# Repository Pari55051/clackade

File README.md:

# 🎮 Clackade — LED the games begin!
a mini arcade in a gameboy style look, with 4 games inter-switchable by long-pressing the first button.

---

## Included Games

1. Simon Says: memory game where a sequence is shown and you have to press the exact same one

2. Whack-a-LED: click the corresponding button to the led before the timer runs out (like Whack a Mole)

3. LED Chase: use the D-pad shaped buttons to navigate to the glowing led as fast as possible

4. Code Cracker: try to guess a randomly code like a detective

---

## Images (or screenshots :P)

### Schematic

---

### PCB Layout

---

### 3D View

---

## How It Works (also acts as a BOM)

- Microcontroller: Seeed XIAO RP2040  
- Buttons: 4x tactile keyboard keys
- LEDs: 4x single-color (+ resistors)
- Mode Switching: Long press on top button triggers the game select loop

---

## Credits

- Made by [U.N. Owen](https://github.com/pari55051)
- Slack ID:  U08TH3JV9V4 (for hackclub's slack)
- Made for: [Pathfinder - Hackclub's YSWS](http://pathfinder.hackclub.com/)

> the drill and gerber files are in the production folder in folders drill an gerbers respectively

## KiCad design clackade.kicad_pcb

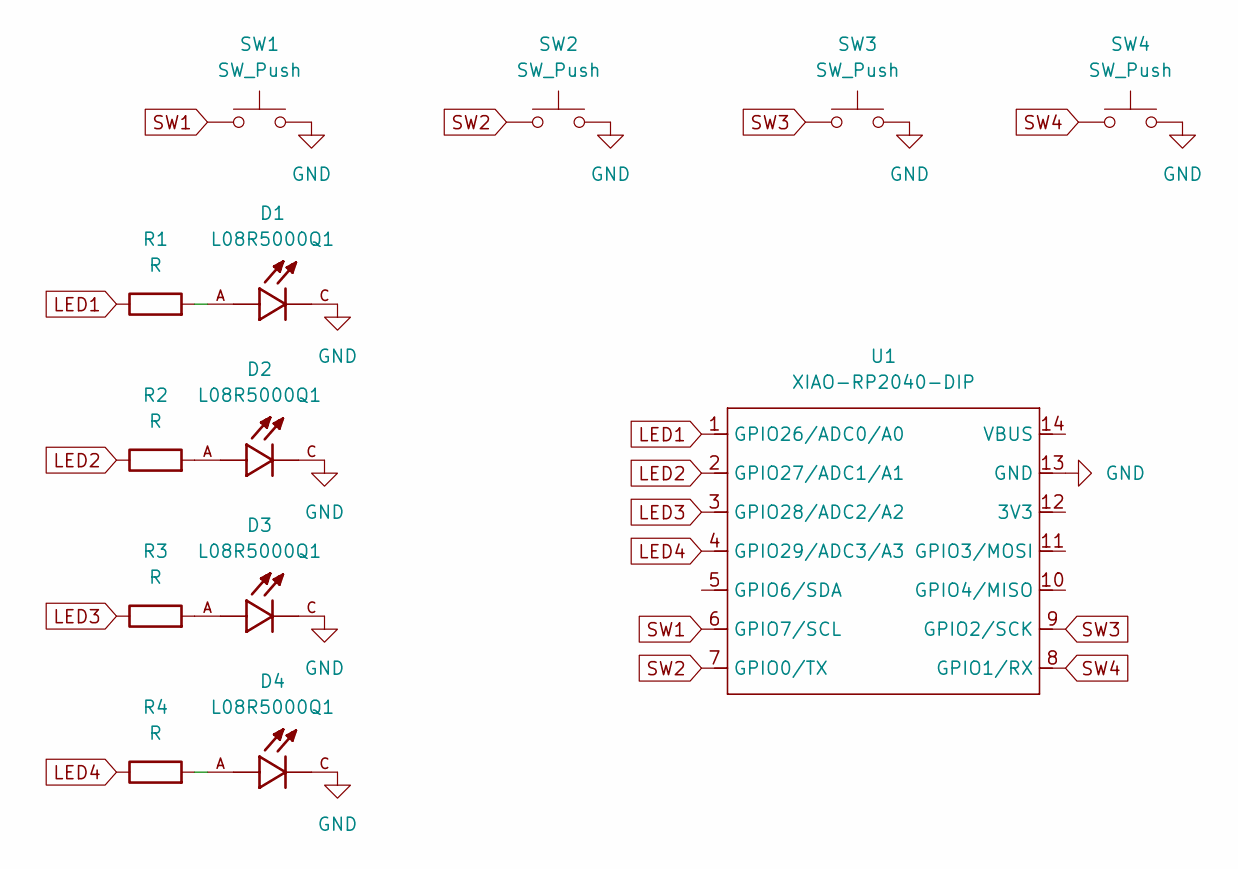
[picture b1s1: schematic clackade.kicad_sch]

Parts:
D1, D2, D3, D4: L08R5000Q1; LEDRD254W57D500H1070; PARTREV NA
R1, R2, R3, R4: R; R_Axial_DIN0204_L3.6mm_D1.6mm_P1.90mm_Vertical
SW1, SW2, SW3, SW4: SW_Push; SW_Cherry_MX_1.00u_PCB
U1: XIAO-RP2040-DIP

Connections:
GND: D1.C, D2.C, D3.C, D4.C, SW1.2, SW2.2, SW3.2, SW4.2, U1.13 (GND)
LED1: R1.1, U1.1 (GPIO26/ADC0/A0)
LED2: R2.1, U1.2 (GPIO27/ADC1/A1)
LED3: R3.1, U1.3 (GPIO28/ADC2/A2)
LED4: R4.1, U1.4 (GPIO29/ADC3/A3)
unnamed: D1.A, R1.2
unnamed: D2.A, R2.2
unnamed: D3.A, R3.2
unnamed: D4.A, R4.2
SW1: SW1.1, U1.6 (GPIO7/SCL)
SW2: SW2.1, U1.7 (GPIO0/TX)
SW3: SW3.1, U1.9 (GPIO2/SCK)
SW4: SW4.1, U1.8 (GPIO1/RX)

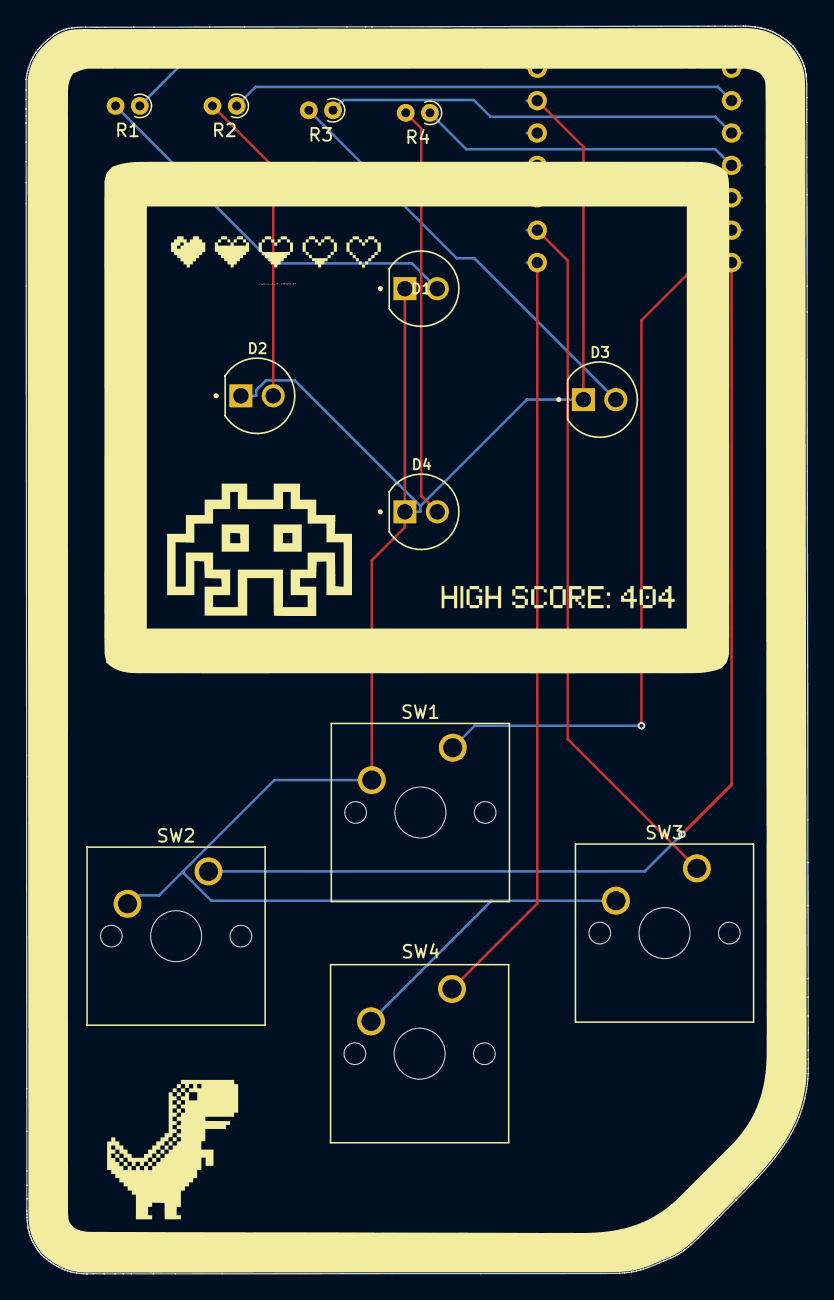
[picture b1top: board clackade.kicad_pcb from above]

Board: 2 copper layers, 61.3 x 97.9 mm, 13 parts (1 on the bottom side), 13 nets.
